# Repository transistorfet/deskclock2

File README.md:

DeskClock 2
===========

###### *Started July 31, 2022*

A desktop companion device for displaying status and controlling things without interrupting flow.
This is a replacement to my previous deskclock project which was originally built in 2009 and later
revamped with an Arduino in 2012.

The new design has an LCD screen, 8 CherryMX buttons, a temperature sensor, an IR receiver, and a
USB connection to my desktop computer.  The controller is a
[Adafruit Feather STM32F405 Express](https://learn.adafruit.com/adafruit-stm32f405-feather-express)
programmed using the Arudino framework.  The computer is running
[Nerve](http://jabberwocky.ca/projects/nerve/), which can perform actions in response to the
buttons, and display information like the current time, current song playing on my computer, and
indoor and outdoor temperature (where the outdoor temperature is broadcast from another computer,
which receives it from a wireless sensor outside).  The buttons are currently configured to control
the music player on my computer, as well as toggle some lights in my computer room.

Custom PCB
----------

Above is the assembled board.  It was designed in November 2022, and assembled in December.

Top down view of the board without the LCD resting on top.  It's a pretty simple design with
an MCP23008 I2C GPIO chip for reading the buttons.

On the bottom, you can see the Kali solderless keyboard button sockets, which are compatible with
CherryMX switches.  They were surprisingly easy to install, align, and solder, using a pre-made
KiCAD footprint.  The sockets snap snugly into the board with no room to wiggle.  I also stuck
some rubber feet to the bottom to clear the sockets from touching the desk, and also to keep it in
place when pressing buttons.

The assembled board with the LCD floating (not securely attached). On the monitor above, you can
see the Python program's log messages showing it receiving the outdoor temperature and sending it
to DeskClock2, and querying the current song to be displayed.

A mistake was made on the board for the IR receiver, which has the power pins reversed.  I attached
a 3 pin header to the board, and with some shrink wrap on one of the pins, bent the power pins to
be reversed when plugged in.

Prototype
---------

Above is the prototype, with the old deskclock to be replaced visible in the background

The prototype is built using an Adafruit
[Feather STM32F405 Express](https://learn.adafruit.com/adafruit-stm32f405-feather-express) with two
[NeoKeys](https://www.adafruit.com/product/4980) and a
[2.8 inch LCD](https://www.adafruit.com/product/2090).

Programming with Arduino
------------------------

In the Arduino IDE:

- select board "Generic STM32F4 Series"
- select board part number "Adafruit Feather STM32F405"
- select USB support "CDC (generic 'Serial' supersede USART)
- select upload method "STM32CubeProgrammer (DFU)"

To put the device in programming mode, hold down the reset button on the Feather, and the Flash button
on the board, and then release the reset button first.

Communication
-------------

The Feather appears as a generic serial-over-USB device.  The protocol is a very simple text format
where each line has a sub-device name/number, followed by an equals sign, and then the data.  For a
button, the device would send "B5=1" when the button is pressed, and "B5=0" when released, where the
number in the name corresponds to the button number between 0 and 7.  The temperature is sent back
as "T0=23.0" where the value is in Celsius.

For the LCD, each of 5 lines is drawn with a separate line to allow them to be updated independently
to avoid flicker due to the slow updated time of the LCD over SPI.  Each line has the form
"L2=Some Text" where the number is the line number to updated, between 0 and 4.  The text can
contain a simple escape code for setting the text colour, of the form "\x1B[3m" which would set the
colour to "3" (green).

The LCD is a passive device, displaying whatever the computer tells it to.  The temperature has to
be sent to the computer, and the computer needs to update the LCD with that information to display
it.  On the Nerve/Computer side, the temperature is also data logged along with other sensors around
the house, so that they can all be displayed on a graph through the web interface.

The IR sensor returns data as "I0=N:40:1", where "N" is NEC protocol, "40" is the address number of
the remote control, and "1" in the command code.

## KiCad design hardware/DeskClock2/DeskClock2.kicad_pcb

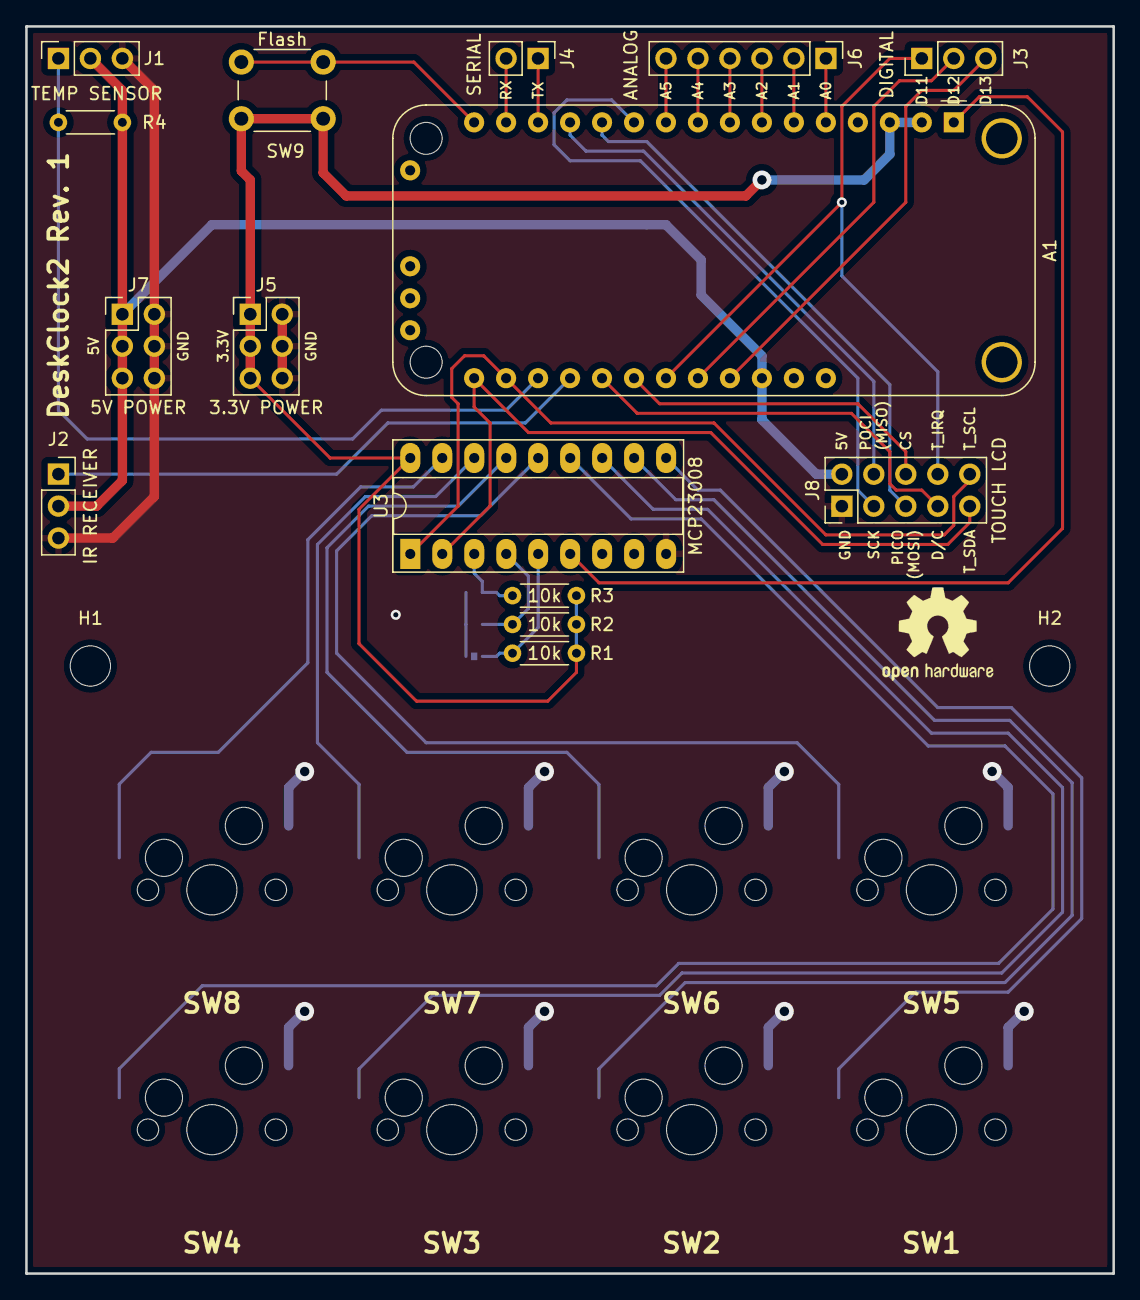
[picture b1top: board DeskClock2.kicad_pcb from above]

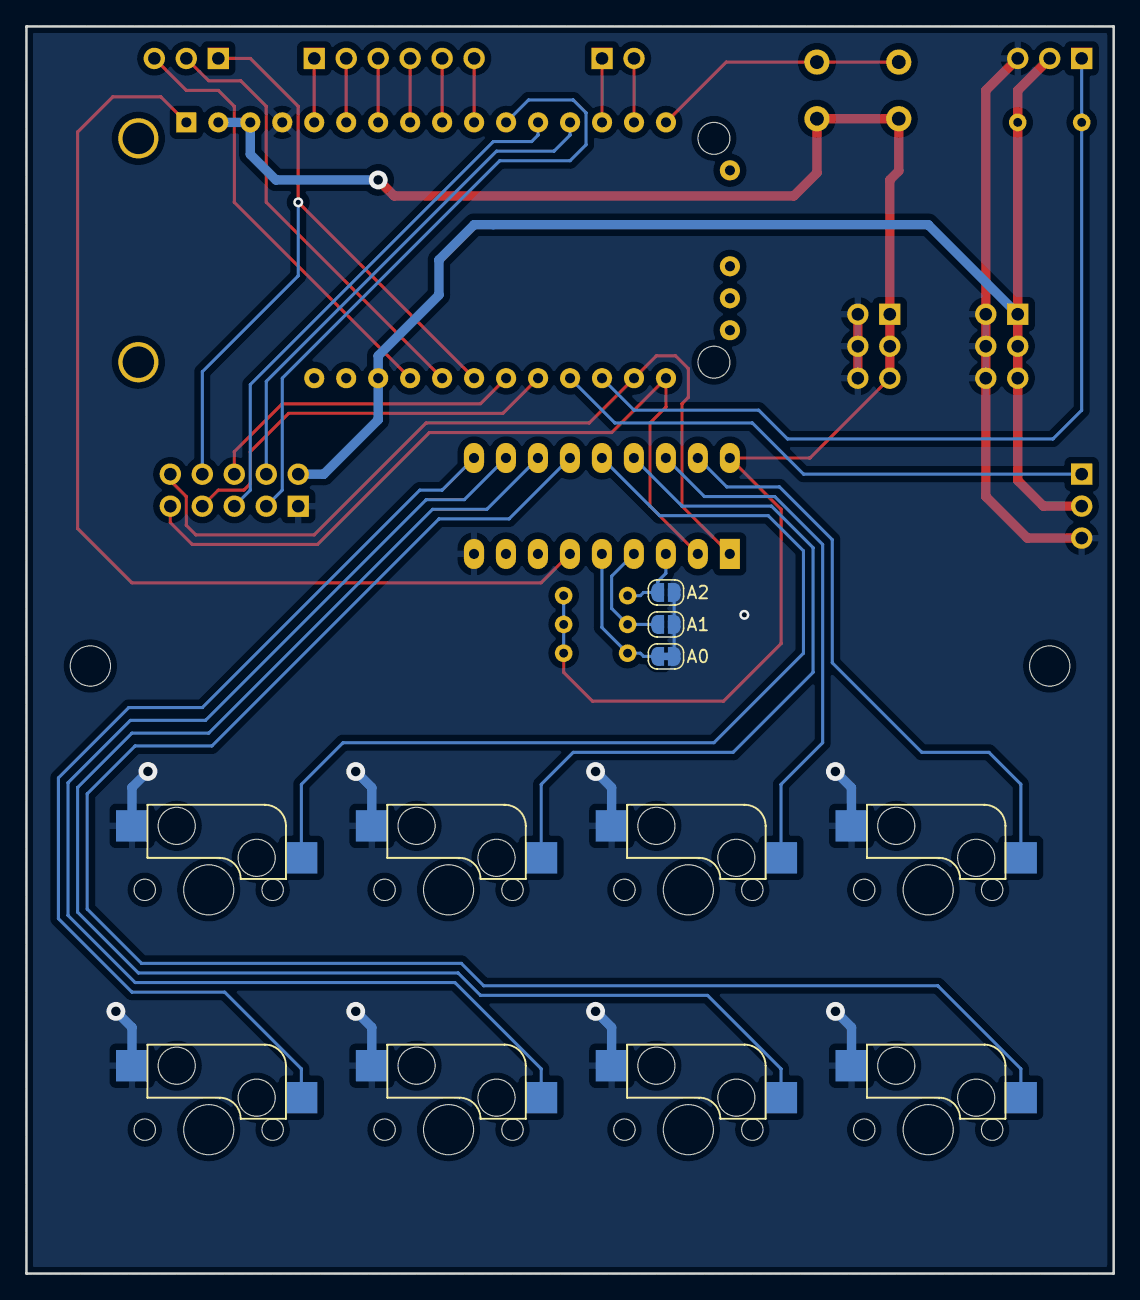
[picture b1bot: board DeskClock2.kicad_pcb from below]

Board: 2 copper layers, 86.4 x 99.1 mm, 29 parts (11 on the bottom side), 36 nets.

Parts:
A1: Adafruit_Feather_STM32F405_Express; Adafruit_Feather_M0_RFM_WithMountingHoles
H1, H2: MountingHole; MountingHole_3.2mm_M3_DIN965
J1: TEMP SENSOR; PinSocket_1x03_P2.54mm_Vertical
J2: IR RECEIVER; PinSocket_1x03_P2.54mm_Vertical
J3: DIGITAL; PinHeader_1x03_P2.54mm_Vertical
J4: SERIAL; PinHeader_1x02_P2.54mm_Vertical
J5: 3.3V POWER; PinHeader_2x03_P2.54mm_Vertical
J6: ANALOG; PinHeader_1x06_P2.54mm_Vertical
J7: 5V POWER; PinHeader_2x03_P2.54mm_Vertical
J8: TOUCH LCD; PinHeader_2x05_P2.54mm_Vertical
JP1: A0; SolderJumper-2_P1.3mm_Bridged_RoundedPad1.0x1.5mm
JP2: A1; SolderJumper-2_P1.3mm_Open_RoundedPad1.0x1.5mm
JP3: A2; SolderJumper-2_P1.3mm_Open_RoundedPad1.0x1.5mm
R1, R2, R3: 10k; R_Axial_DIN0204_L3.6mm_D1.6mm_P5.08mm_Horizontal
R4: 4.7k; R_Axial_DIN0204_L3.6mm_D1.6mm_P5.08mm_Horizontal
SW1, SW2, SW3, SW4, SW5, SW6, SW7, SW8: SW_Push; Kailh_MX_Socket
SW9: Flash; SW_PUSH_6mm
U1: Adfruit_LCD_Breakout_Touch; OSHW-Logo2_9.8x8mm_SilkScreen
U3: MCP23008; DIP-18_W7.62mm_Socket_LongPads

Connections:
+3.3V: A1.2 (3V3), A1.3 (3V3), J5.1, J5.3, J5.5, R1.1, R2.1, R3.1, SW9.2, U3.18 (VDD)
+5V: A1.26 (USB), J1.2, J2.2, J7.1, J7.3, J7.5, J8.2, R4.2
GND: A1.4 (GND), J1.3, J2.3, J5.2, J5.4, J5.6, J7.2, J7.4, J7.6, J8.1, JP1.1 (A), JP2.1 (A), JP3.1 (A), SW1.2, SW2.2, SW3.2, SW4.2, SW5.2, SW6.2, SW7.2, SW8.2, U3.9 (VSS)
IR_IO: A1.20 (D6), J2.1
LCD_CS: A1.22 (D10), J8.6
LCD_DC: A1.21 (D9), J8.7
LCD_PICO: A1.12 (PICO/D23), J8.5
LCD_POCI: A1.13 (POCI/D22), J8.4
LCD_SCK: A1.11 (SCK/D24), J8.3
unnamed: A1.5 (DAC0/A0), J6.1
unnamed: A1.6 (A1), J6.2
unnamed: A1.7 (A2), J6.3
unnamed: A1.8 (A3), J6.4
unnamed: A1.9 (A4), J6.5
unnamed: A1.10 (A5), J6.6
unnamed: A1.14 (RX/D0), J4.1
unnamed: A1.15 (TX/D1), J4.2
unnamed: A1.16 (B0), SW9.1
unnamed: A1.24 (D12), J3.2
unnamed: A1.25 (D13), J3.3
unnamed: JP1.2 (B), R1.2, U3.5 (A0)
unnamed: JP2.2 (B), R2.2, U3.4 (A1)
unnamed: JP3.2 (B), R3.2, U3.3 (A2)
unnamed: SW1.1, U3.10 (GP0)
unnamed: SW2.1, U3.11 (GP1)
unnamed: SW3.1, U3.12 (GP2)
unnamed: SW4.1, U3.13 (GP3)
unnamed: SW5.1, U3.14 (GP4)
unnamed: SW6.1, U3.15 (GP5)
unnamed: SW7.1, U3.16 (GP6)
unnamed: SW8.1, U3.17 (GP7)
RESET: A1.1 (~RESET), U3.6 (~RESET)
SCL: A1.18 (SCL/D21), J8.10, U3.1 (SCL)
SDA: A1.17 (SDA/D20), J8.9, U3.2 (SDA)
T_1WR: A1.19 (D5), J1.1, R4.1
T_IRQ: A1.23 (D11), J3.1, J8.8

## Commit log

2022-08-16 Initial commit after lots of testing
2022-08-18 Added temperature sensor
2022-11-14 Added first draft of hardware and PCB design
2022-12-02 Revision 1 complete
2022-12-03 Changed capitalization of file names in hardware/
2022-12-11 Completed assembly of the board
2022-12-11 Updated with IR receiver
2022-12-11 Updated errata
